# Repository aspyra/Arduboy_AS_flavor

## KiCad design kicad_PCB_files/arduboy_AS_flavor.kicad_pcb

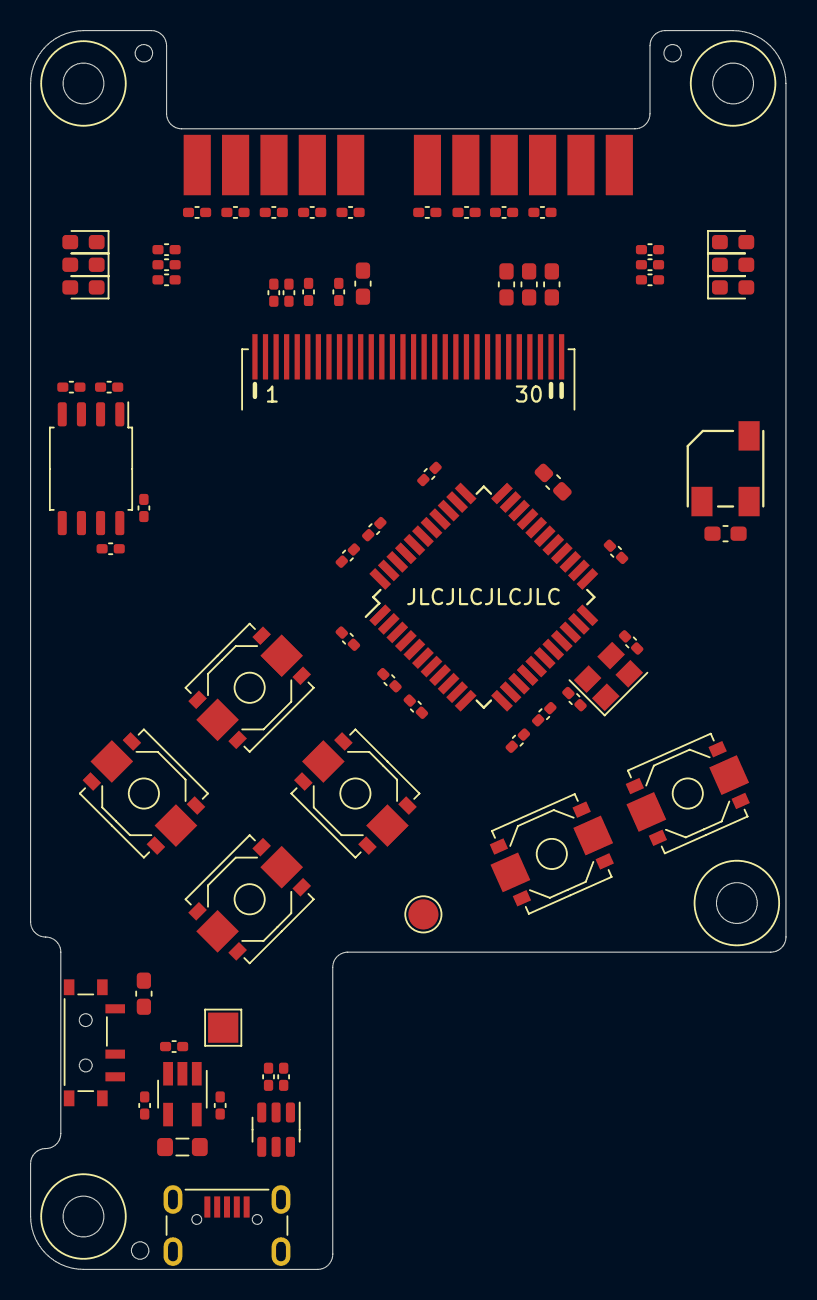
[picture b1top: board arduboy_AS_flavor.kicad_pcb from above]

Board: 4 copper layers, 50.0 x 82.0 mm, 78 parts (0 on the bottom side), 66 nets, no tracks yet.

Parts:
BZ1: Buzzer; Buzzer_KLJ-5020
C1, C7, C8: 10uF; 0603_HandSolder
C2, C3: 12pF; 0402_HandSolder
C4, C16, C17, C18, C19, C20, C21, C22: 100nF; 0402_HandSolder
C5, C6, C10, C11, C12, C13, C28: 1uF; 0402_HandSolder
C9, C15: 4.7uF; 0603_HandSolder
C14: 2.2uF; 0603_HandSolder
D2: Red; LED_0603_1608Metric_Pad1.05x0.95mm_HandSolder
D3: Green; LED_0603_1608Metric_Pad1.05x0.95mm_HandSolder
D4: Blue; LED_0603_1608Metric_Pad1.05x0.95mm_HandSolder
D7, D8, D9: Yellow; LED_0603_1608Metric_Pad1.05x0.95mm_HandSolder
FB1: 100R @ 100MHz; L_0805_2012Metric_Pad1.05x1.20mm_HandSolder
H1, H2, H3: JLC; JLCPCB_assembly_hole
H4, H5, H6, H7: M2; M2_mounting_hole
J1: SSD1306; SSD1306_30pin_P0.7mm
J2: Expansion_port_NEW; ExpansionPort_SMD
J3: USB_B_Micro; USB_MICRO_B_C456008
R1, R2, R3, R4: 10k; 0402_HandSolder
R5, R6, R7, R8, R18, R19, R22, R23, R24: 120; 0402_HandSolder
R9, R12, R13: 1.2k; 0402_HandSolder
R10, R11: 680; 0402_HandSolder
R14, R16: 4.7k; 0402_HandSolder
R17: 390k; 0603_HandSolder
R20, R21: 22; 0402_HandSolder
SW1: ON/OFF; Switch_DPDT_MSK12CO2-BDM
SW2: UP Button; button_TS-1187A-B-A-B
SW3: DOWN Button; button_TS-1187A-B-A-B
SW4: LEFT Button; button_TS-1187A-B-A-B
SW5: RIGHT Button; button_TS-1187A-B-A-B
SW6: A Button; button_TS-1187A-B-A-B
SW7: B Button; button_TS-1187A-B-A-B
TP1: Lipo [+]; TestPoint_Pad_2.0x2.0mm
TP16: Lipo (-); TestPoint_Pad_D2.0mm
U1: ATmega32U4-AU; TQFP-44_10x10mm_P0.8mm
U2: W25Q128JVSIQ; SOIC-8_5.23x5.23mm_P1.27mm
U3: SRV05-4; SOT-23-6
U4: TP4054; SOT-23-5_HandSoldering
Y1: 16MHz; Crystal_SMD_3225-4Pin_3.2x2.5mm

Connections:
+5V: C13.1, C17.1, C18.1, D7.2 (A), FB1.1, U1.2 (UVCC), U1.7 (VBUS), U4.4 (VCC)
+BATT: C12.1, SW1.2 (B), TP1.1, U4.3 (BAT)
/PROG: R16.1, U4.5 (PROG)
/USB_D+: J3.3 (D+), R20.1, U3.1 (IO1), U3.6 (IO4)
/USB_D-: J3.2 (D-), R21.1, U3.3 (IO2), U3.4 (IO3)
/~HOLD: R4.2, U2.7 (IO3)
/~WP: R3.2, U2.3 (IO2)
A5: R18.1, U1.41 (PF0)
AREF: C16.1, U1.42 (AREF)
Btn_A: SW6.1, U1.1 (PE6)
Btn_B: SW7.1, U1.28 (PB4)
Btn_DOWN: SW3.1, U1.39 (PF4)
Btn_LEFT: SW4.1, U1.38 (PF5)
Btn_RIGHT: SW5.1, U1.37 (PF6)
Btn_UP: SW2.1, U1.36 (PF7)
D+: R20.2, U1.4 (D+)
D-: R21.2, U1.3 (D-)
GND: C1.2, C2.2, C3.2, C4.2, C7.2, C8.2, C10.2, C11.2, C12.2, C13.2, C14.2, C15.2, C16.2, C17.2, C18.2, C19.2, C20.2, C21.2, C22.2, C28.2, J1.7 (VSS), J1.8 (VSS), J1.10 (BS0), J1.11 (BS1), J1.12 (BS2), J1.16 (R/~W), J1.17 (E/~RD), J2.2, J3.5 (GND), R16.2, R17.2, SW2.2, SW3.2, SW4.2, SW5.2, SW6.2, SW7.2, TP16.1, U1.5 (UGND), U1.15 (GND), U1.23 (GND), U1.33 (~HWB/PE2), U1.35 (GND), U1.43 (GND), U2.4 (GND), U3.2 (VN), U4.2 (GND), Y1.2, Y1.4
LED_B: R11.2, U1.29 (PB5)
LED_G: R10.2, U1.12 (PB7)
LED_R: R9.2, U1.30 (PB6)
MISO: R19.1, U1.11 (PB3), U2.2 (DO(IO1))
MOSI: J1.19 (D1), R22.1, U1.10 (PB2), U2.5 (DI(IO0))
unnamed: BZ1.1 (-), C9.2
unnamed: C5.1, J1.2 (C2P)
unnamed: C5.2, J1.3 (C2N)
unnamed: C6.1, J1.4 (C1P)
unnamed: C6.2, J1.5 (C1N)
unnamed: C14.1, J1.27 (VCMH)
unnamed: C15.1, J1.28 (VCC)
unnamed: D2.1 (K), R9.1
unnamed: D3.1 (K), R10.1
unnamed: D4.1 (K), R11.1
unnamed: D7.1 (K), R14.1
unnamed: D8.1 (K), R12.1
unnamed: D9.1 (K), R13.1
unnamed: J1.26 (IREF), R17.1
unnamed: J2.3, R24.2
unnamed: J2.4, R23.2
unnamed: J2.5, R22.2
unnamed: J2.6, R19.2
unnamed: J2.8, R18.2
unnamed: J2.9, R8.2
unnamed: J2.10, R7.2
unnamed: J2.11, R6.2
unnamed: J2.12, R5.2
OLED_CS: J1.13 (~CS), U1.26 (PD6)
OLED_DC: J1.15 (~DC), U1.25 (PD4)
OLED_RST: J1.14 (~RST), U1.27 (PD7)
RST: R1.2, R24.1, U1.13 (~RESET)
RX: R8.1, U1.20 (PD2)
RX_LED: R12.2, U1.8 (PB0)
SCK: J1.18 (D0), U1.9 (PB1)
SCL: R7.1, U1.18 (PD0)
SCLK: R23.1, U2.6 (CLK)
SDA+FCS: R2.2, R6.1, U1.19 (PD1), U2.1 (~CS)
SPKR1: C9.1, U1.31 (PC6)
SPKR2: BZ1.2 (+), U1.32 (PC7)
TX: R5.1, U1.21 (PD3)
TX_LED: R13.2, U1.22 (PD5)
UCAP: C28.1, U1.6 (UCAP)
VBUS: FB1.2, J3.1 (VBUS), U3.5 (VP)
VCC: C1.1, C4.1, C7.1, C8.1, C10.1, C11.1, C19.1, C20.1, C21.1, C22.1, D2.2 (A), D3.2 (A), D4.2 (A), D8.2 (A), D9.2 (A), J1.6 (VBAT), J1.9 (VDD), J2.1, R1.1, R2.1, R3.1, R4.1, SW1.1 (A), U1.14 (VCC), U1.24 (AVCC), U1.34 (VCC), U1.44 (AVCC), U2.8 (VCC)
XTAL1: C2.1, U1.17 (XTAL1), Y1.3
XTAL2: C3.1, U1.16 (XTAL2), Y1.1
~CHRG: R14.2, U4.1 (~CHRG)

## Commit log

2021-10-08 Initial commit - Imported KiCAD files
2021-10-09 Added SSH1106 pinout picture
2021-10-09 Added 1.3 inch SSH1106 dimensions
2021-10-09 Multiple schematic changes Added SSH1106 connector (30 pin 0.7mm pitch)
2021-10-10 Added SSD1306, SSH1106 pinouts & capacitor recommendations
2021-10-10 v0.1 schematic Added screen connectors Added testpoints Exported v0.1 schematic as .pdf
2021-10-11 Changed screen capacitor's size and value PCB mockup added
2021-10-11 PCB changes - Button footprints for clicky OR silent switches
2021-10-12 Added footprints: JLCPCB assembly hole and my logo
2021-10-12 Added mechanical mounting points Continued PCB placement feasibility
2021-10-20 Changed reset circuit Continued PCB placement feasibility Changed piezo footprint
2021-10-21 Changed mosfet pullup/pulldown resistor values
2021-10-22 Power switch with latch - simulation added
2021-10-22 Power switch v2.0 simulation added
2021-10-22 Power switch 2.0 update
2023-05-02 Major changes, practically v2
    Changed board shape
    Changed a great part of the schematic
    Component placement done
